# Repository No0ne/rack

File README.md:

# Pico RACK - <ins>R</ins>etro <ins>A</ins>dapter for <ins>C</ins>omputer <ins>K</ins>eyboards
A PCB designed to work with the ps2x2pico project which simplifies the hardware setup and provides for multiple target computer keyboard interfaces at the same time.

Concept: This adapter would connect to a Raspberry Pi Pico running the code from the [ps2x2pico project](https://github.com/No0ne/ps2x2pico). It would allow the user to connect a USB keyboard to a vintage computer and switch between PS/2 (AT), XT, Early Mac, and ADB keyboard interfaces.

Status: The schematic for this project and the changes necessary to support it are still in the early phases.

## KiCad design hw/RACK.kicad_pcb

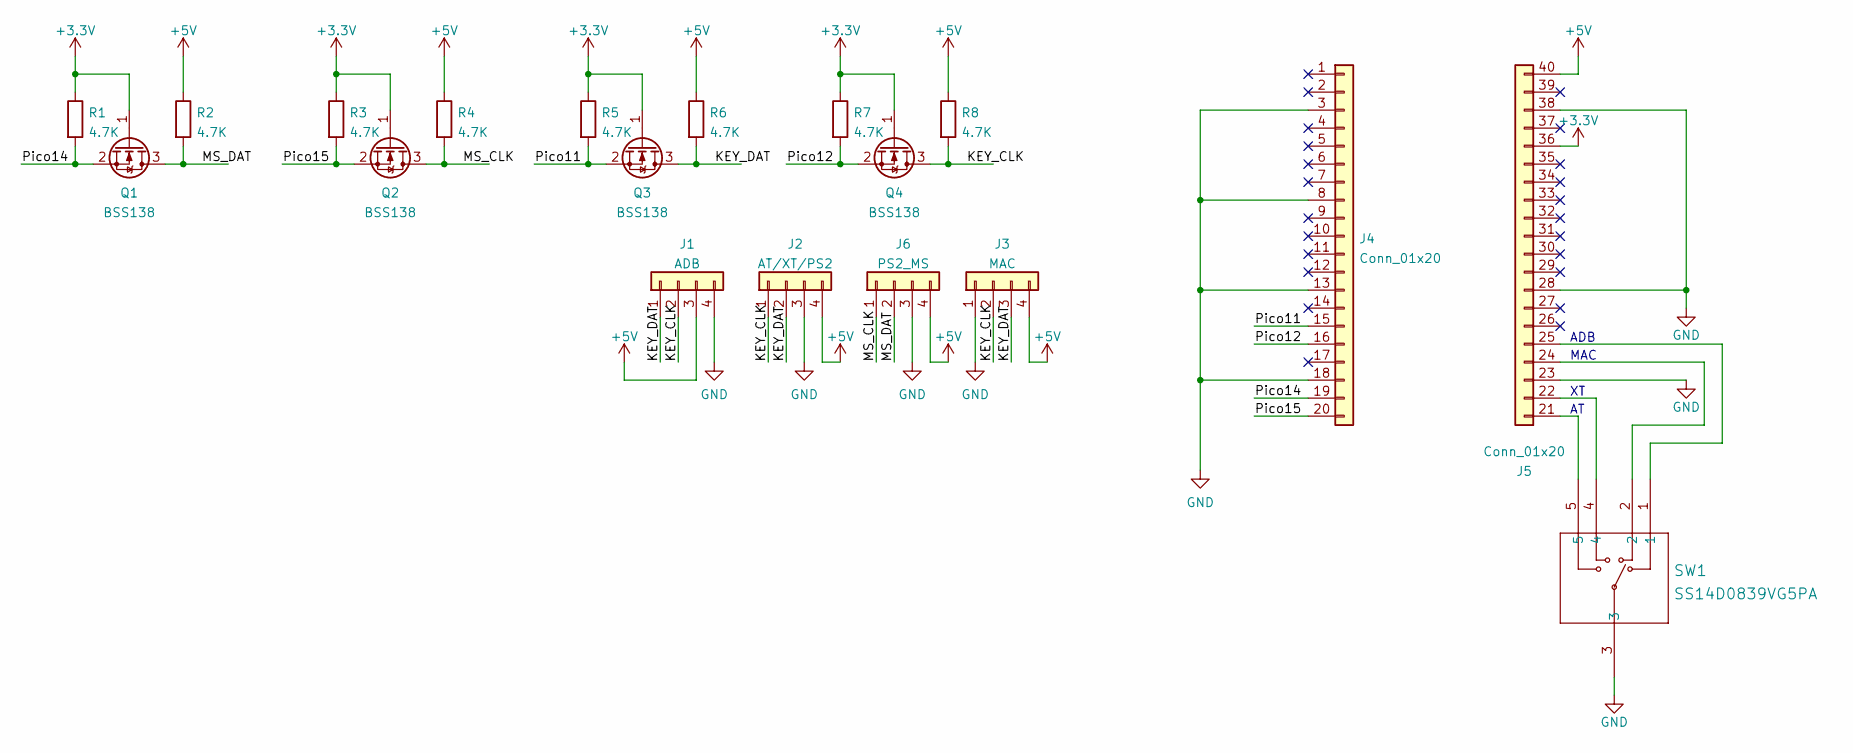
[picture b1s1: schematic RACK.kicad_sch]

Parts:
J1: ADB; TE_5749181-1
J2: AT/XT/PS2; PinHeader_1x04_P2.54mm_Vertical
J3: MAC; PinHeader_1x04_P2.54mm_Vertical
J4, J5: Conn_01x20; PinSocket_1x20_P2.54mm_Vertical
J6: PS2_MS; PinHeader_1x04_P2.54mm_Vertical
Q1, Q2, Q3, Q4: BSS138; SOT-23
R1, R2, R3, R4, R5, R6, R7, R8: 4.7K; R_0603_1608Metric
SW1: SS14D0839VG5PA; SS-14D0839_CNK

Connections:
+3V3: J5.36, Q1.1 (G), Q2.1 (G), Q3.1 (G), Q4.1 (G), R1.1, R3.1, R5.1, R7.1
+5V: J1.3, J2.4, J3.4, J5.40, J6.4, R2.1, R4.1, R6.1, R8.1
/KEY_CLK: J1.2, J2.1, J3.2, Q4.3 (D), R8.2
/KEY_DAT: J1.1, J2.2, J3.3, Q3.3 (D), R6.2
/MS_CLK: J6.1, Q2.3 (D), R4.2
/MS_DAT: J6.2, Q1.3 (D), R2.2
/Pico11: J4.15, Q3.2 (S), R5.2
/Pico12: J4.16, Q4.2 (S), R7.2
/Pico14: J4.19, Q1.2 (S), R1.2
/Pico15: J4.20, Q2.2 (S), R3.2
GND: J1.4, J2.3, J3.1, J4.3, J4.8, J4.13, J4.18, J5.23, J5.28, J5.38, J6.3, SW1.3
unnamed: J5.25, SW1.1
unnamed: J5.24, SW1.2
unnamed: J5.22, SW1.4
unnamed: J5.21, SW1.5

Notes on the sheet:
ADB
MAC

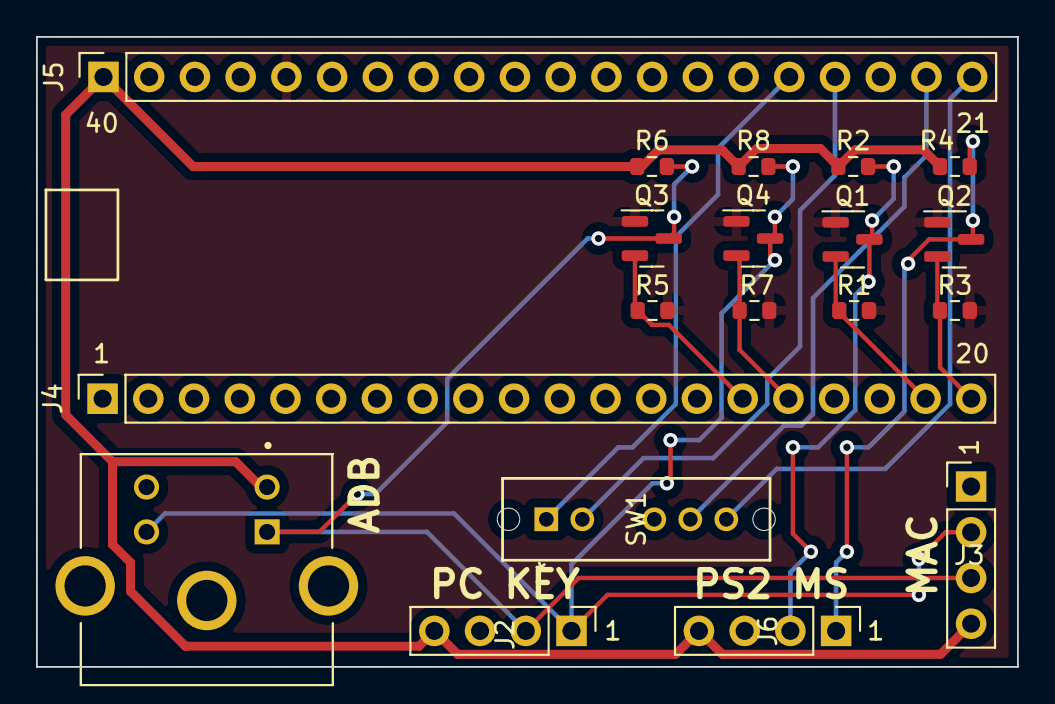
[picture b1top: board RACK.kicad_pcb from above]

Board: 2 copper layers, 54.5 x 35.0 mm, 19 parts (0 on the bottom side), 15 nets.

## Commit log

2024-04-09 moved content from aaronnewcomb/ps2x2pico-adapter
2024-04-10 Full KiCAD project with PCB
2024-04-10 pico_project.py -x -f pio rack
2024-04-10 moved testbranch from ps2x2pico
2024-04-10 reformat macphy.pio
2024-04-17 add ps2x2pico as submodule
